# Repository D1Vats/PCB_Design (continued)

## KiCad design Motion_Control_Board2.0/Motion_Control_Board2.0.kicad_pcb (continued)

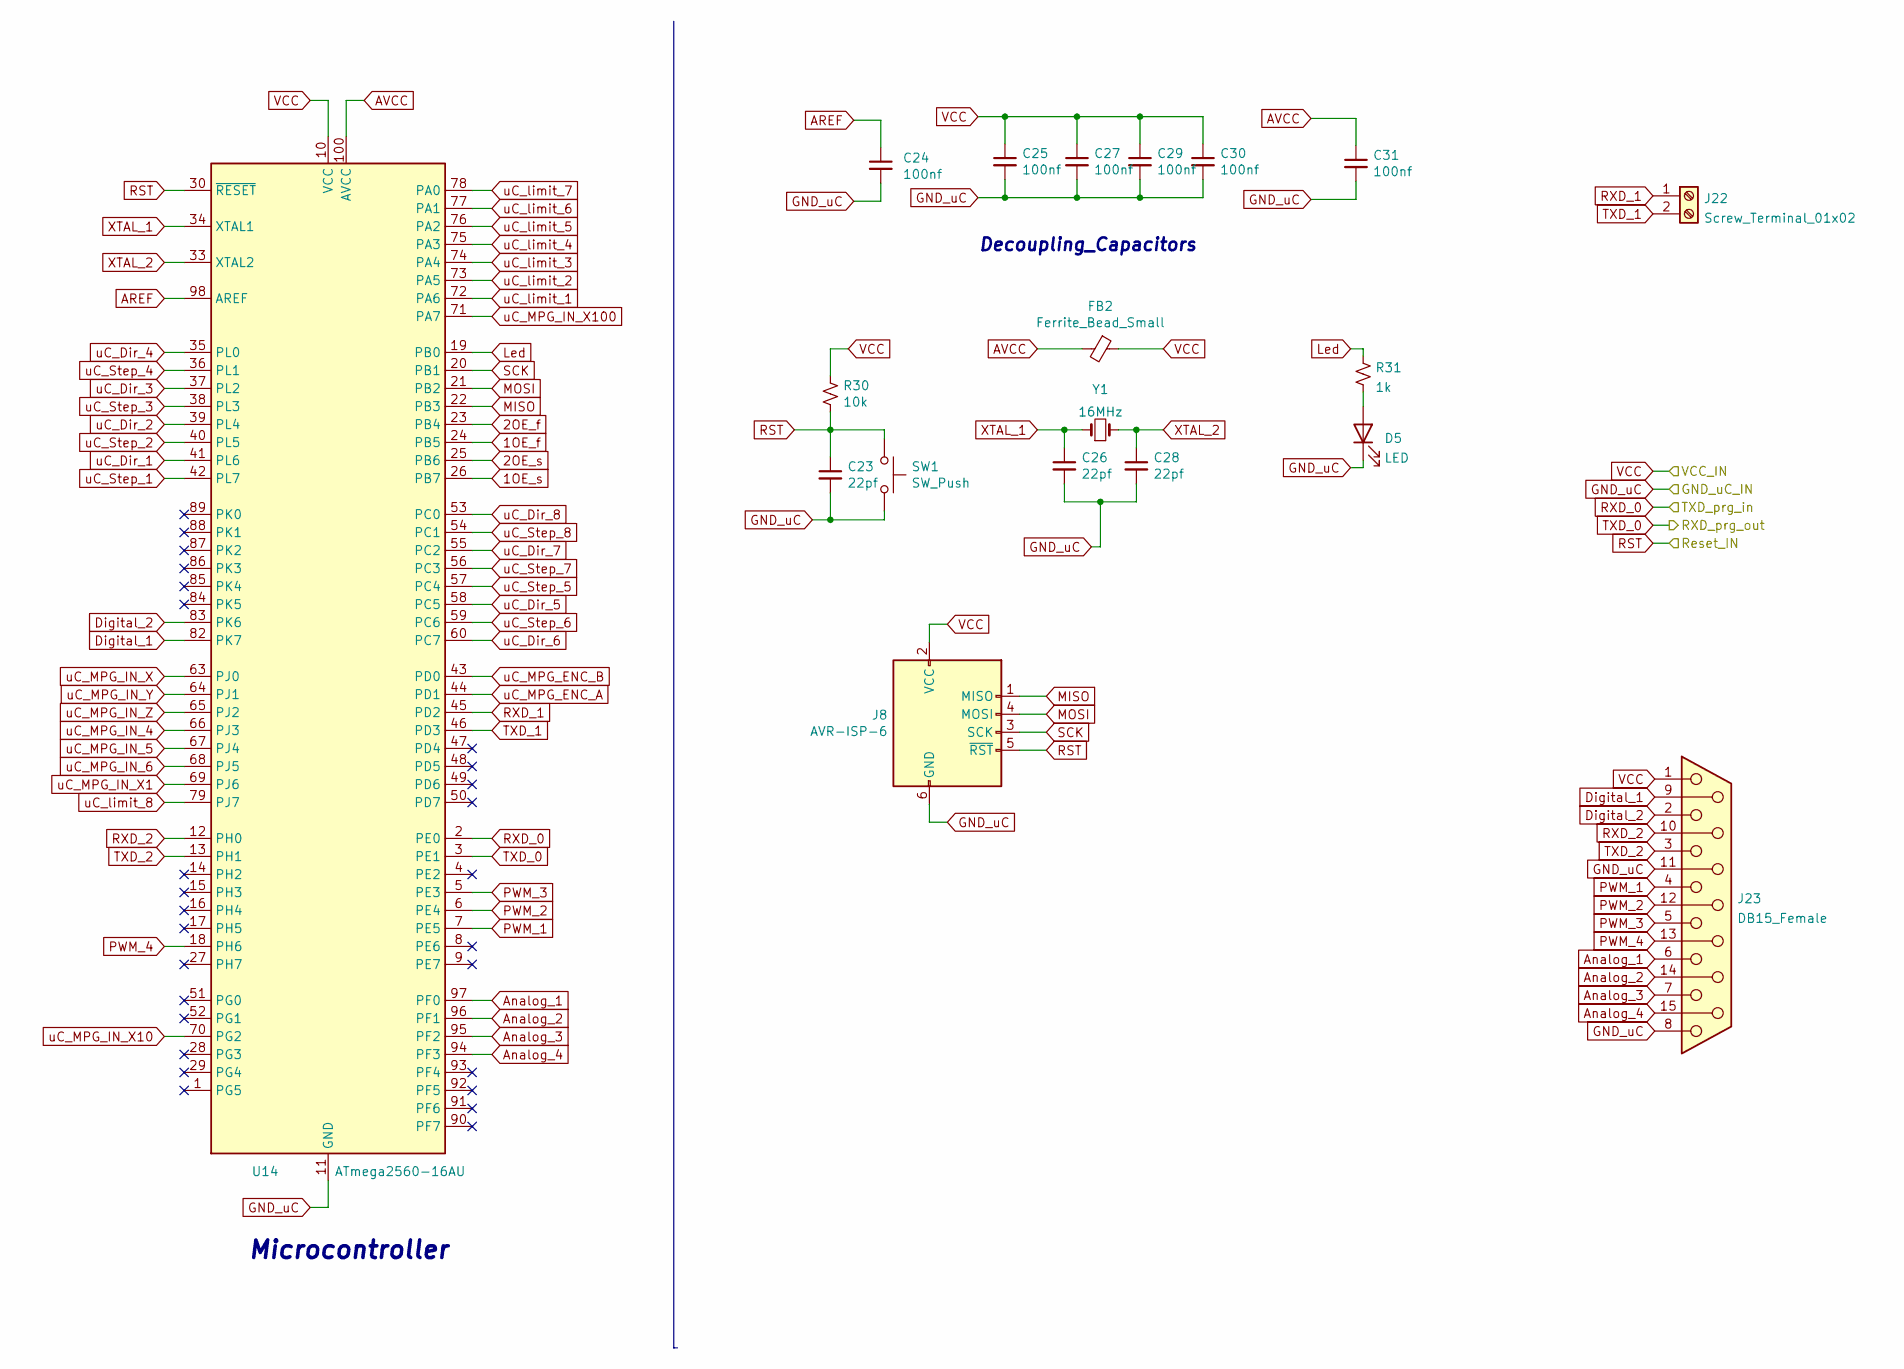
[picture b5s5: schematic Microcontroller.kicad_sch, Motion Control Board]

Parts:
C23, C26, C28: 22pf; C_0805_2012Metric
C24, C25, C27, C29, C30, C31: 100nf; C_0805_2012Metric
D5: LED; LED_0805_2012Metric
FB2: Ferrite_Bead_Small; R_0805_2012Metric
J8: AVR-ISP-6; PinHeader_2x03_P2.54mm_Vertical
J22: Screw_Terminal_01x02; TerminalBlock_4Ucon_1x02_P3.50mm_Vertical
J23: DB15_Female; DSUB-15_Female_Horizontal_P2.77x2.84mm_EdgePinOffset7.70mm_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
R30: 10k; R_0805_2012Metric
R31: 1k; R_0805_2012Metric
SW1: SW_Push; SW_PUSH_6mm
U14: ATmega2560-16AU; TQFP-100_14x14mm_P0.5mm
Y1: 16MHz; Crystal_HC49-4H_Vertical

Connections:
1OE_f: U14.24 (PB5); also elsewhere on the board
1OE_s: U14.26 (PB7); also elsewhere on the board
2OE_f: U14.23 (PB4); also elsewhere on the board
2OE_s: U14.25 (PB6); also elsewhere on the board
5V_OUT_1: C25.1, C27.1, C29.1, C30.1, FB2.1, J8.2 (VCC), J23.1, R30.1, U14.10 (VCC), U14.31 (VCC), U14.61 (VCC), U14.80 (VCC); also elsewhere on the board
AREF: C24.1, U14.98 (AREF)
AVCC: C31.1, FB2.2, U14.100 (AVCC)
Analog_1: J23.6, U14.97 (PF0)
Analog_2: J23.14, U14.96 (PF1)
Analog_3: J23.7, U14.95 (PF2)
Analog_4: J23.15, U14.94 (PF3)
DTR_prg: C23.1, J8.5 (~RST), R30.2, SW1.1, U14.30 (~RESET); also elsewhere on the board
Digital_1: J23.9, U14.82 (PK7)
Digital_2: J23.2, U14.83 (PK6)
Led: R31.1, U14.19 (PB0)
MISO: J8.1 (MISO), U14.22 (PB3)
MOSI: J8.4 (MOSI), U14.21 (PB2)
MPG_GND: C23.2, C24.2, C25.2, C26.2, C27.2, C28.2, C29.2, C30.2, C31.2, D5.1 (K), J8.6 (GND), J23.8, J23.11 (P111), SW1.2, U14.11 (GND), U14.32 (GND), U14.62 (GND), U14.81 (GND), U14.99 (GND); also elsewhere on the board
unnamed: D5.2 (A), R31.2
PWM_1: J23.4, U14.7 (PE5)
PWM_2: J23.12, U14.6 (PE4)
PWM_3: J23.5, U14.5 (PE3)
PWM_4: J23.13, U14.18 (PH6)
RXD_0: U14.2 (PE0); also elsewhere on the board
RXD_1: J22.1, U14.45 (PD2)
RXD_2: J23.10, U14.12 (PH0)
SCK: J8.3 (SCK), U14.20 (PB1)
TXD_0: U14.3 (PE1); also elsewhere on the board
TXD_1: J22.2, U14.46 (PD3)
TXD_2: J23.3, U14.13 (PH1)
XTAL_1: C26.1, U14.34 (XTAL1), Y1.1
XTAL_2: C28.1, U14.33 (XTAL2), Y1.2
uC_Dir_1: U14.41 (PL6); also elsewhere on the board
uC_Dir_2: U14.39 (PL4); also elsewhere on the board
uC_Dir_3: U14.37 (PL2); also elsewhere on the board
uC_Dir_4: U14.35 (PL0); also elsewhere on the board
uC_Dir_5: U14.58 (PC5); also elsewhere on the board
uC_Dir_6: U14.60 (PC7); also elsewhere on the board
uC_Dir_7: U14.55 (PC2); also elsewhere on the board
uC_Dir_8: U14.53 (PC0); also elsewhere on the board
uC_MPG_ENC_A: U14.44 (PD1); also elsewhere on the board
uC_MPG_ENC_B: U14.43 (PD0); also elsewhere on the board
uC_MPG_IN_4: U14.66 (PJ3); also elsewhere on the board
uC_MPG_IN_5: U14.67 (PJ4); also elsewhere on the board
uC_MPG_IN_6: U14.68 (PJ5); also elsewhere on the board
uC_MPG_IN_X: U14.63 (PJ0); also elsewhere on the board
uC_MPG_IN_X1: U14.69 (PJ6); also elsewhere on the board
uC_MPG_IN_X10: U14.70 (PG2); also elsewhere on the board
uC_MPG_IN_X100: U14.71 (PA7); also elsewhere on the board
uC_MPG_IN_Y: U14.64 (PJ1); also elsewhere on the board
uC_MPG_IN_Z: U14.65 (PJ2); also elsewhere on the board
uC_Step_1: U14.42 (PL7); also elsewhere on the board
uC_Step_2: U14.40 (PL5); also elsewhere on the board
uC_Step_3: U14.38 (PL3); also elsewhere on the board
uC_Step_4: U14.36 (PL1); also elsewhere on the board
uC_Step_5: U14.57 (PC4); also elsewhere on the board
uC_Step_6: U14.59 (PC6); also elsewhere on the board
uC_Step_7: U14.56 (PC3); also elsewhere on the board
uC_Step_8: U14.54 (PC1); also elsewhere on the board
uC_limit_1: U14.72 (PA6); also elsewhere on the board
uC_limit_2: U14.73 (PA5); also elsewhere on the board
uC_limit_3: U14.74 (PA4); also elsewhere on the board
uC_limit_4: U14.75 (PA3); also elsewhere on the board
uC_limit_5: U14.76 (PA2); also elsewhere on the board
uC_limit_6: U14.77 (PA1); also elsewhere on the board
uC_limit_7: U14.78 (PA0); also elsewhere on the board
uC_limit_8: U14.79 (PJ7); also elsewhere on the board

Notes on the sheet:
Microcontroller
Decoupling_Capacitors

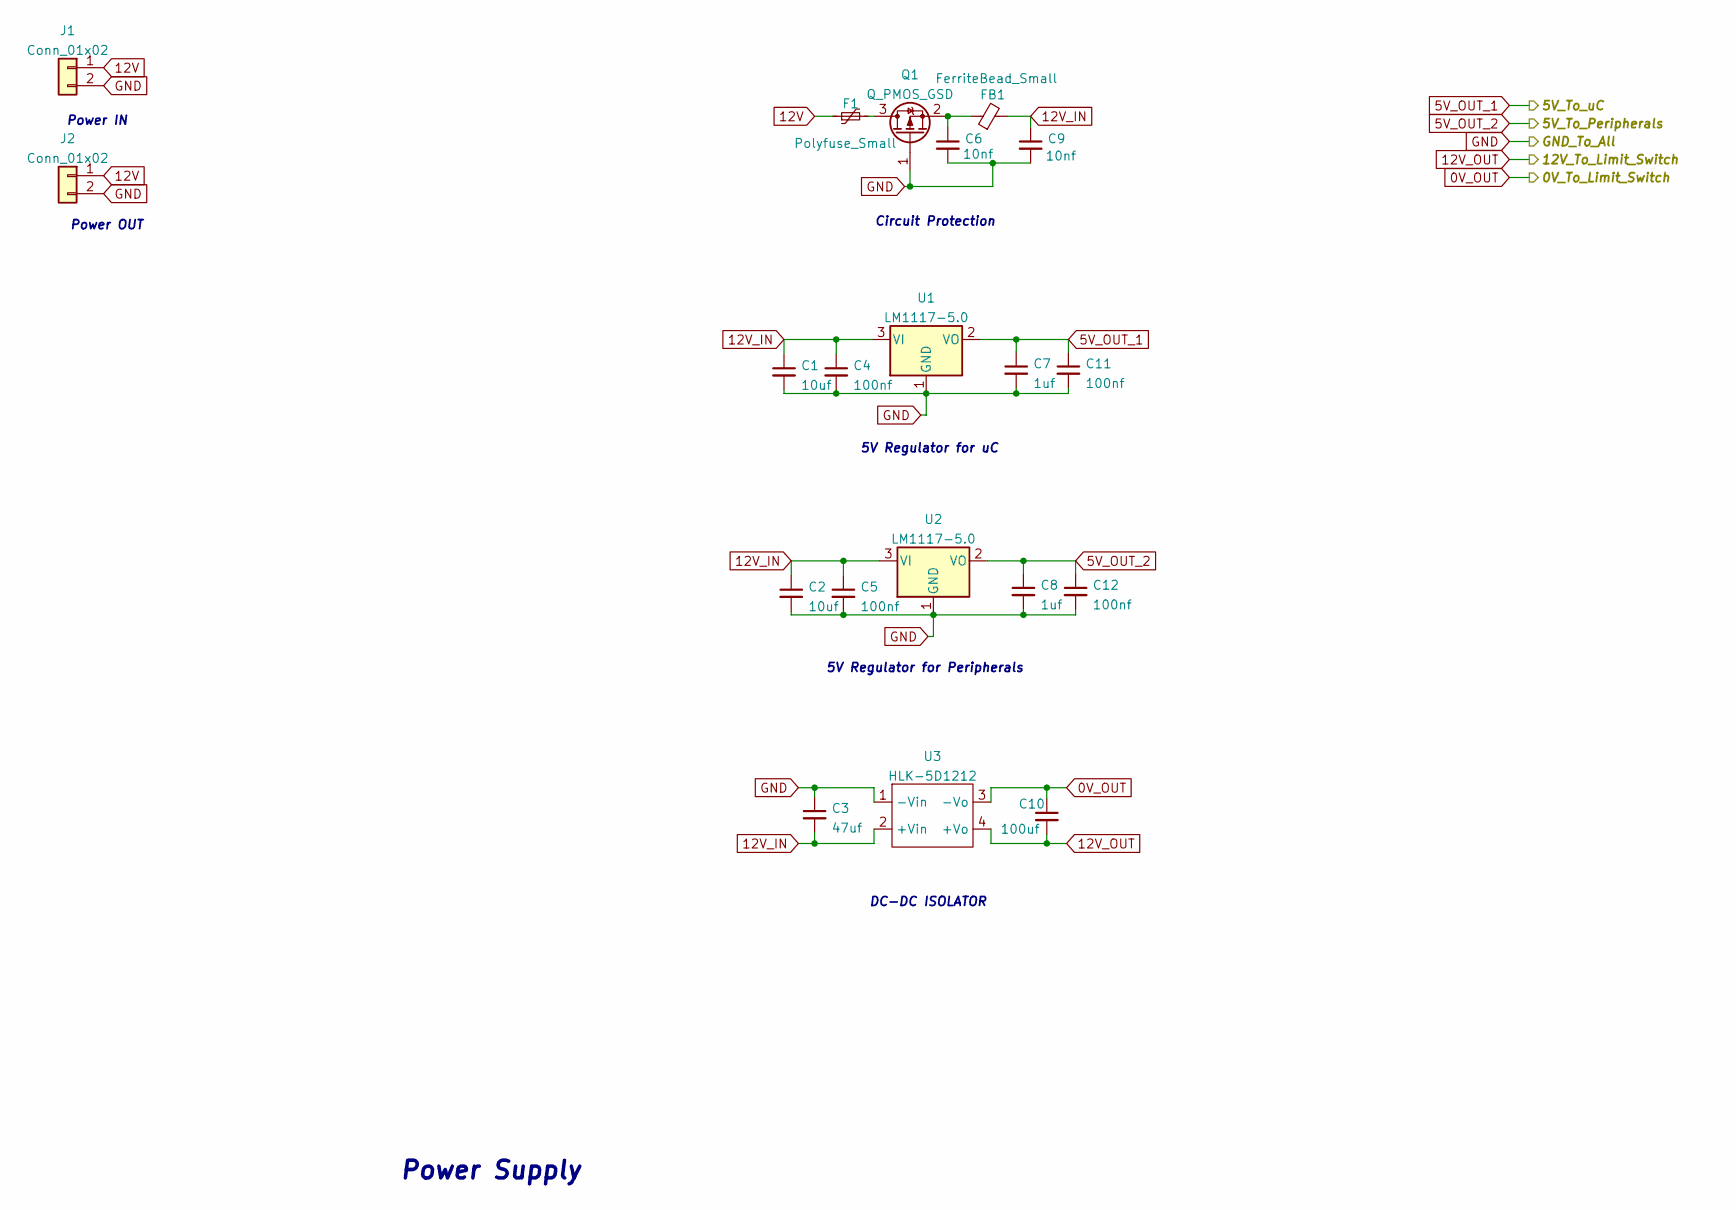
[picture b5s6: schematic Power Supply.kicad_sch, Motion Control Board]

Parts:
C1, C2: 10uf; C_0805_2012Metric
C3: 47uf; C_0805_2012Metric
C4, C5, C11, C12: 100nf; C_0805_2012Metric
C6, C9: 10nf; C_0805_2012Metric
C7, C8: 1uf; C_0805_2012Metric
C10: 100uf; C_0805_2012Metric
F1: Polyfuse_Small; Fuse_0805_2012Metric
FB1: FerriteBead_Small; R_0805_2012Metric
J1, J2: Conn_01x02; TerminalBlock_4Ucon_1x02_P3.50mm_Vertical
Q1: Q_PMOS_GSD; SOT-23W
U1, U2: LM1117-5.0; SOT-223
U3: HLK-5D1212

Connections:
0V_OUT: C10.1, U3.3 (-Vo); also elsewhere on the board
5V_OUT_1: C7.1, C11.1, U1.2 (VO); also elsewhere on the board
5V_OUT_2: C8.1, C12.1, U2.2 (VO); also elsewhere on the board
12V: F1.1, J1.1, J2.1
12V_IN: C1.1, C2.1, C3.2, C4.1, C5.1, C9.1, FB1.2, U1.3 (VI), U2.3 (VI), U3.2 (+Vin)
12V_OUT: C10.2, U3.4 (+Vo); also elsewhere on the board
MPG_GND: C1.2, C2.2, C3.1, C4.2, C5.2, C6.2, C7.2, C8.2, C9.2, C11.2, C12.2, J1.2, J2.2, Q1.1 (G), U1.1 (GND), U2.1 (GND), U3.1 (-Vin); also elsewhere on the board
unnamed: C6.1, FB1.1, Q1.2 (S)
unnamed: F1.2, Q1.3 (D)

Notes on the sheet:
DC-DC ISOLATOR
5V Regulator for uC
5V Regulator for Peripherals
Power OUT
Power Supply
Power IN
Circuit Protection

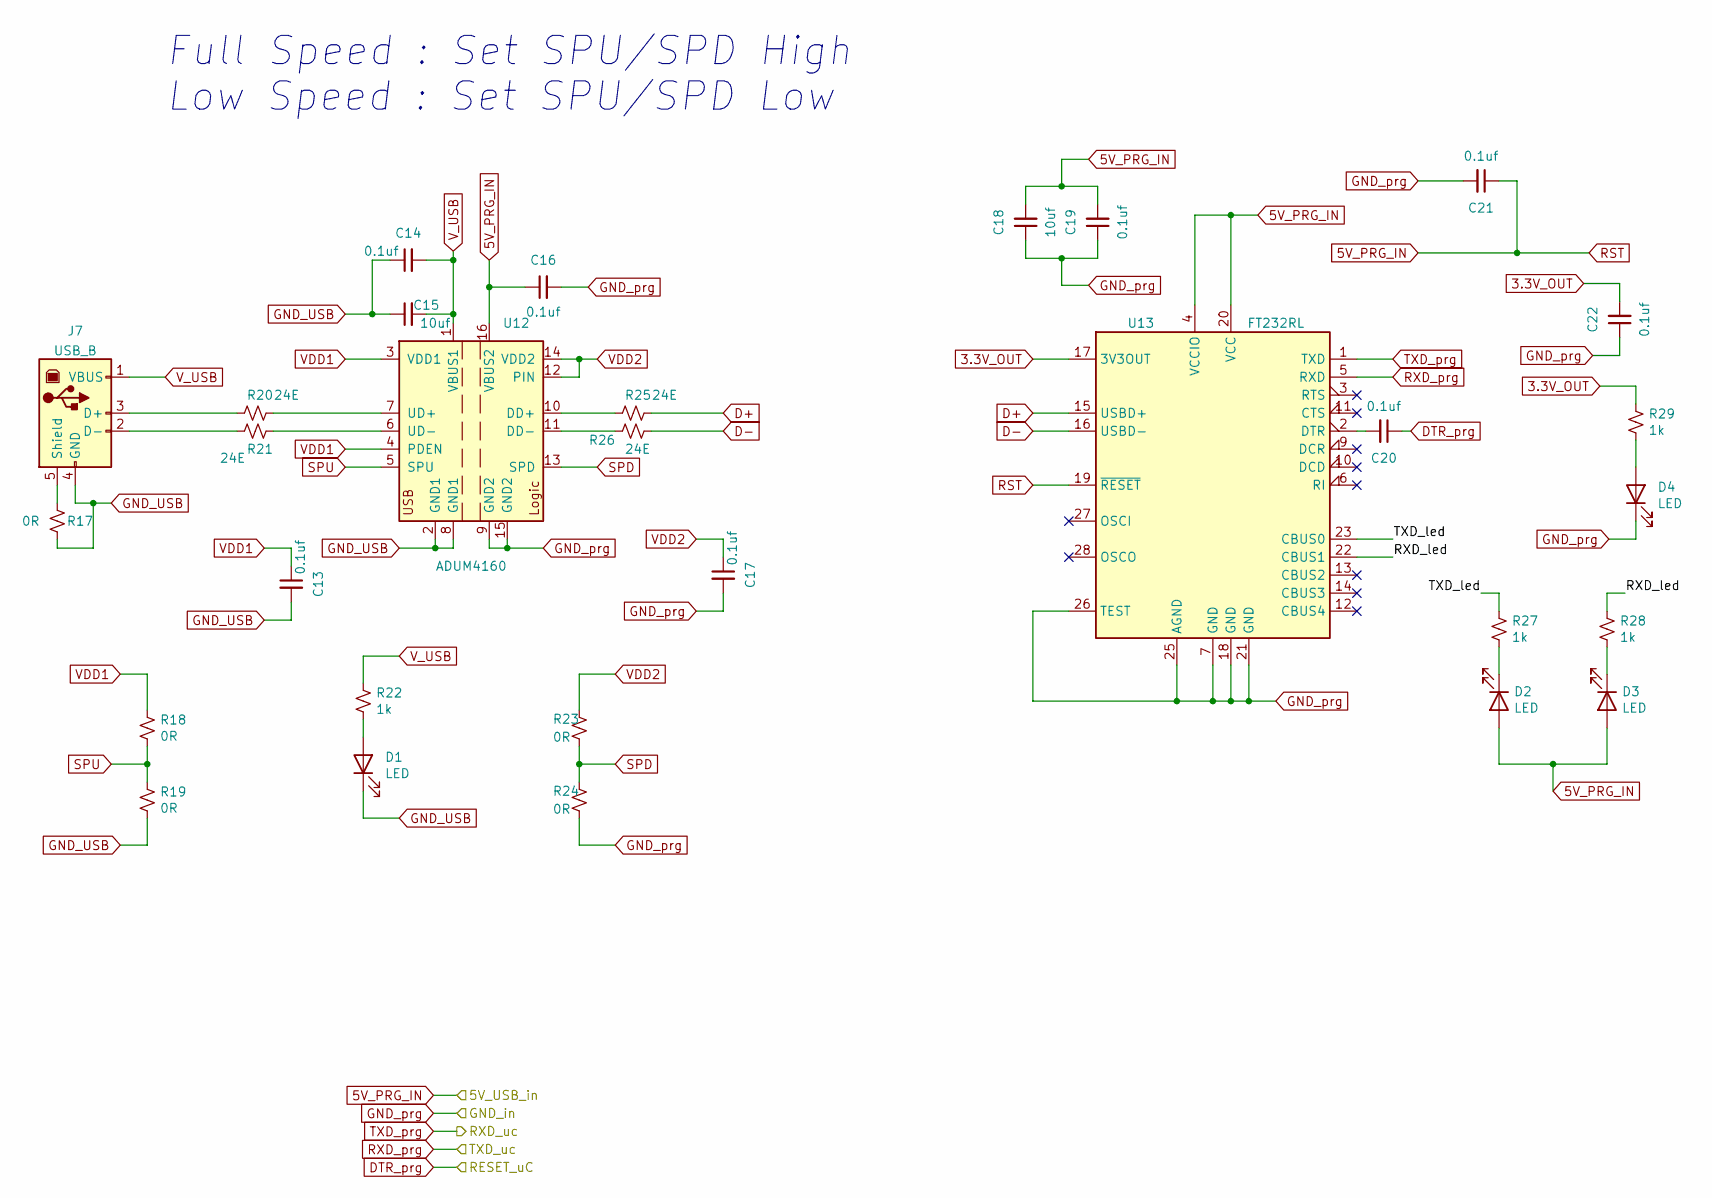
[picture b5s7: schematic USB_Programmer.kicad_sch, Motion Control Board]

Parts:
C13, C14, C16, C17, C19, C20, C21, C22: 0.1uf; C_0805_2012Metric
C15, C18: 10uf; C_0805_2012Metric
D1, D2, D3, D4: LED; LED_0805_2012Metric
J7: USB_B; USB_B_OST_USB-B1HSxx_Horizontal
R17, R18, R19, R23, R24: 0R; R_0805_2012Metric
R20, R21, R25, R26: 24E; R_0805_2012Metric
R22, R27, R28, R29: 1k; R_0805_2012Metric
U12: ADUM4160; SOIC-16W_7.5x10.3mm_P1.27mm
U13: FT232RL; SSOP-28_5.3x10.2mm_P0.65mm

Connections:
3.3V_OUT: C22.2, R29.1, U13.17 (3V3OUT)
5V_OUT_1: C16.1, C18.2, C19.2, C21.1, D2.2 (A), D3.2 (A), U12.16 (VBUS2), U13.4 (VCCIO), U13.19 (~RESET), U13.20 (VCC); also elsewhere on the board
/USB_Programmer/RXD_led: R28.1, U13.22 (CBUS1)
/USB_Programmer/TXD_led: R27.1, U13.23 (CBUS0)
D+: R25.1, U13.15 (USBD+)
D-: R26.1, U13.16 (USBD-)
DTR_prg: C20.1; also elsewhere on the board
GND_USB: C13.2, C14.1, C15.1, D1.1 (K), J7.4 (GND), R17.2, R19.2, U12.2 (GND1), U12.8 (GND1)
MPG_GND: C16.2, C17.2, C18.1, C19.1, C21.2, C22.1, D4.1 (K), R24.2, U12.9 (GND2), U12.15 (GND2), U13.7 (GND), U13.18 (GND), U13.21 (GND), U13.25 (AGND), U13.26 (TEST); also elsewhere on the board
unnamed: C20.2, U13.2 (DTR)
unnamed: D1.2 (A), R22.2
unnamed: D2.1 (K), R27.2
unnamed: D3.1 (K), R28.2
unnamed: D4.2 (A), R29.2
unnamed: J7.2 (D-), R21.2
unnamed: J7.3 (D+), R20.2
unnamed: J7.5 (Shield), R17.1
unnamed: R20.1, U12.7 (UD+)
unnamed: R21.1, U12.6 (UD-)
unnamed: R25.2, U12.10 (DD+)
unnamed: R26.2, U12.11 (DD-)
RXD_0: U13.1 (TXD); also elsewhere on the board
SPD: R23.2, R24.1, U12.13 (SPD)
SPU: R18.2, R19.1, U12.5 (SPU)
TXD_0: U13.5 (RXD); also elsewhere on the board
VDD1: C13.1, R18.1, U12.3 (VDD1), U12.4 (PDEN)
VDD2: C17.1, R23.1, U12.12 (PIN), U12.14 (VDD2)
V_USB: C14.2, C15.2, J7.1 (VBUS), R22.1, U12.1 (VBUS1)

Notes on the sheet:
Full Speed : Set SPU/SPD High Low Speed : Set SPU/SPD Low

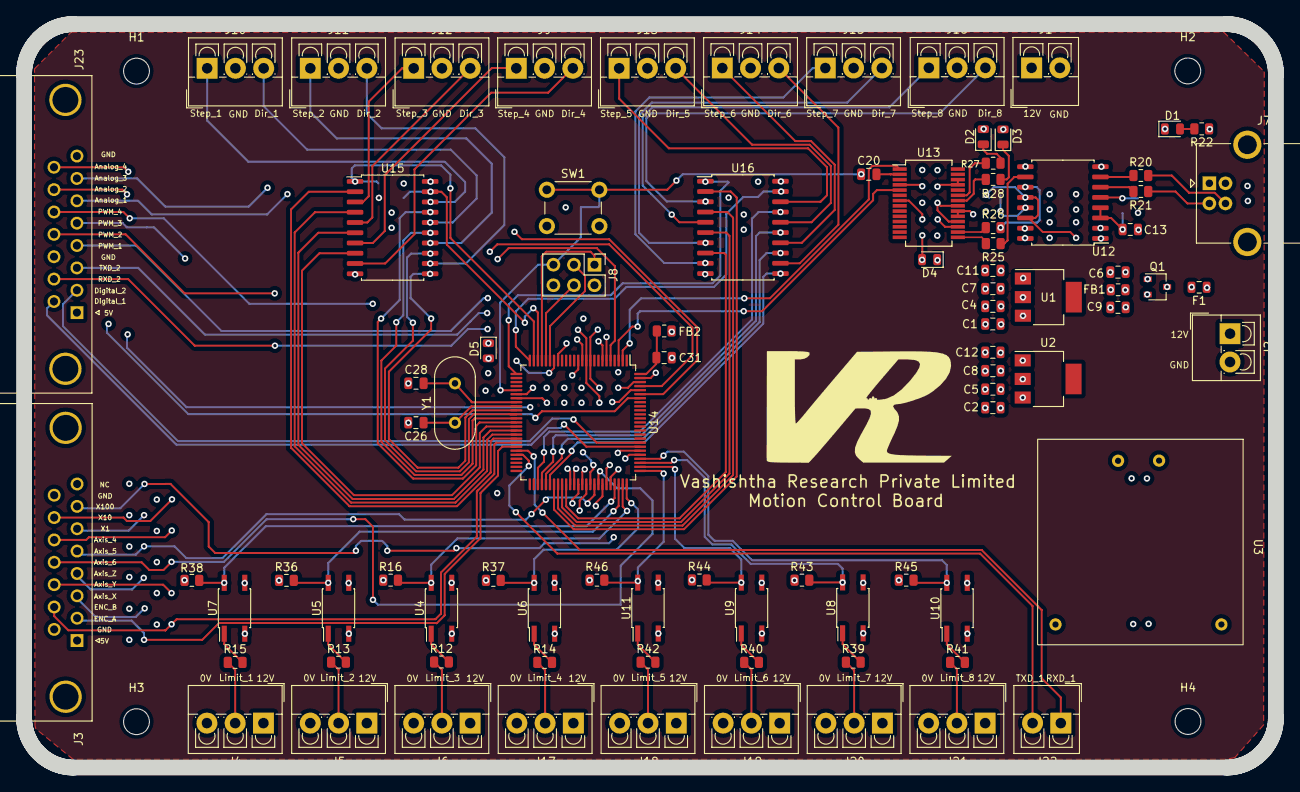
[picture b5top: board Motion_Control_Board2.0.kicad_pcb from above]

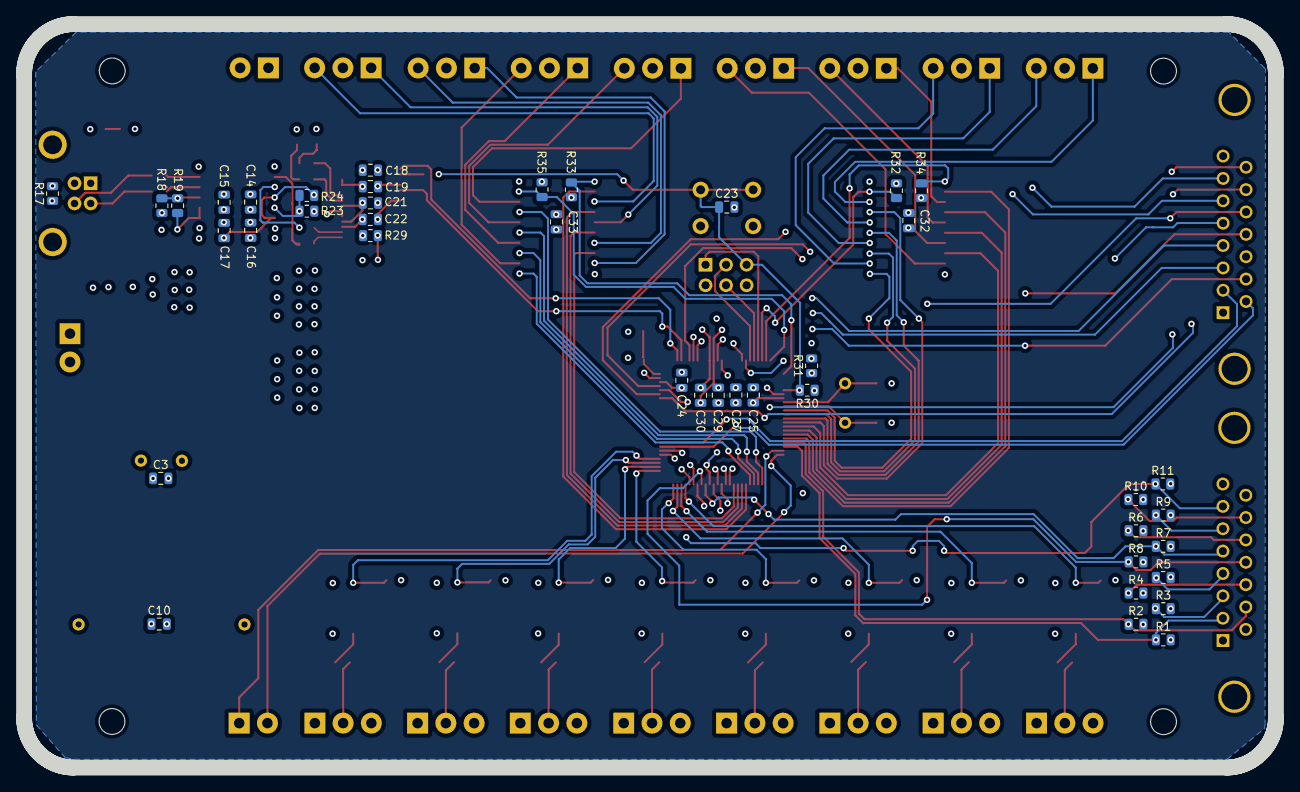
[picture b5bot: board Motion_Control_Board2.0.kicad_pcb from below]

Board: 4 copper layers, 155.0 x 92.1 mm, 133 parts (41 on the bottom side), 129 nets.

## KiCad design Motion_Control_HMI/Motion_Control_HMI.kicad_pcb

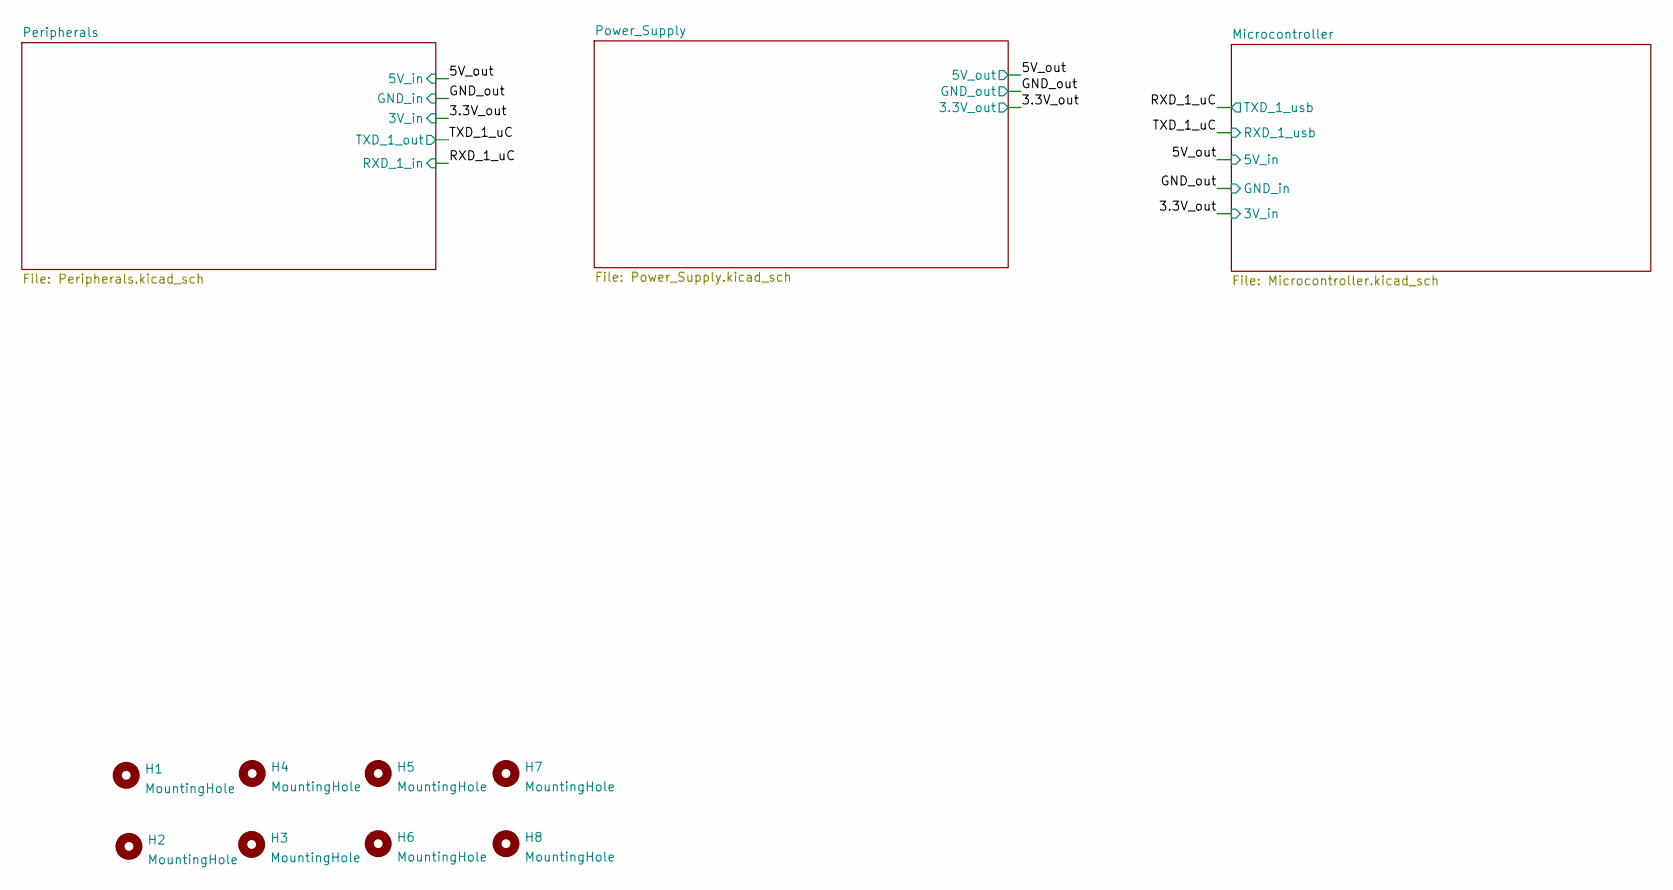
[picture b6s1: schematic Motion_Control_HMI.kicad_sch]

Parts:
H1, H3, H4, H6: MountingHole; MountingHole_4.3mm_M4
H2, H5, H7, H8: MountingHole; MountingHole_3.2mm_M3

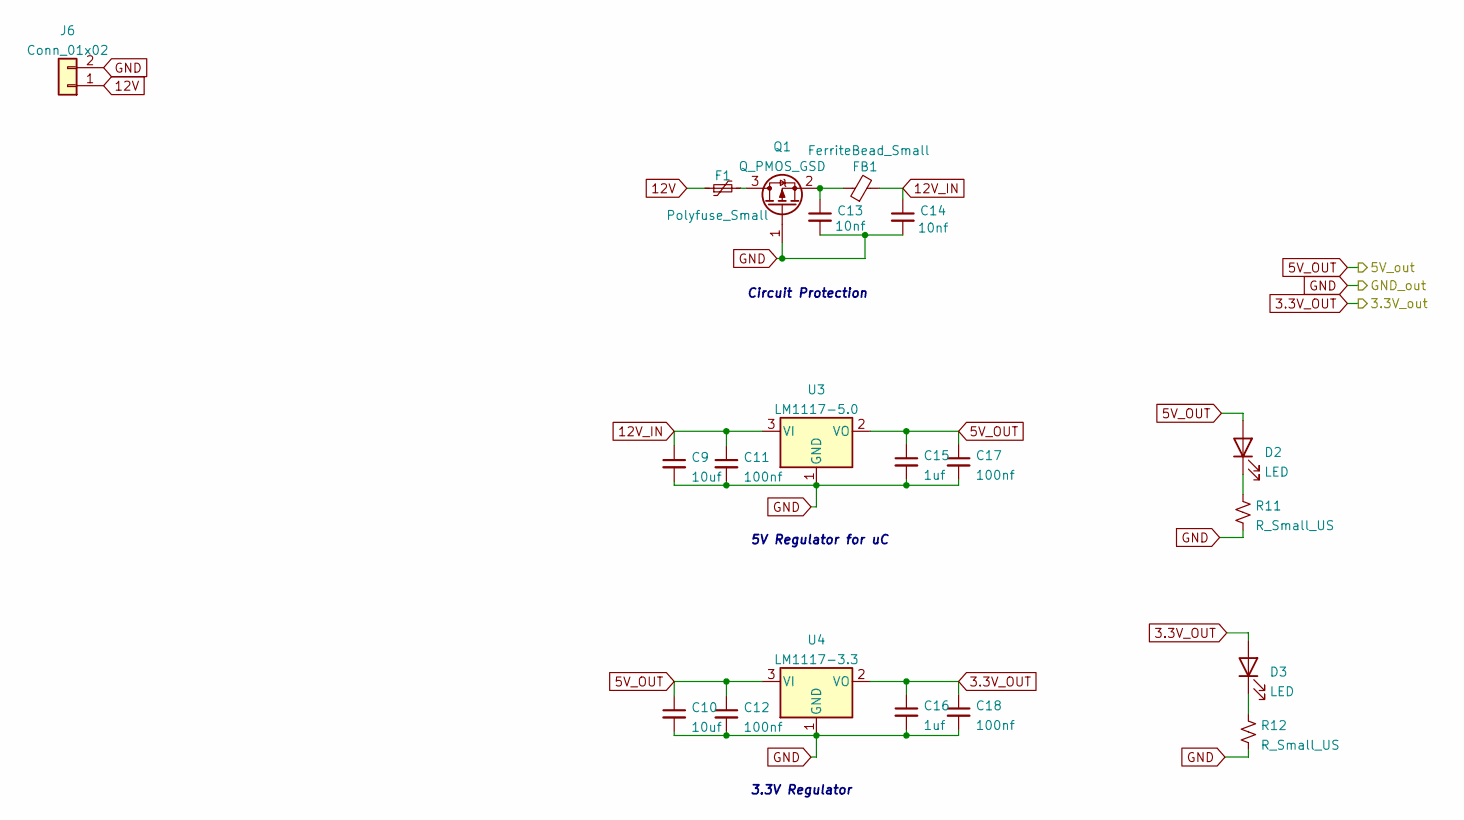
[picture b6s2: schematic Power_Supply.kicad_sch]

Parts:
C9, C10: 10uf; C_0805_2012Metric
C11, C12, C17, C18: 100nf; C_0805_2012Metric
C13, C14: 10nf; C_0805_2012Metric
C15, C16: 1uf; C_0805_2012Metric
D2, D3: LED; LED_0805_2012Metric
F1: Polyfuse_Small; Fuse_0805_2012Metric
FB1: FerriteBead_Small; R_0805_2012Metric
J6: Conn_01x02; JST_EH_B2B-EH-A_1x02_P2.50mm_Vertical
Q1: Q_PMOS_GSD; SOT-23W
R11, R12: R_Small_US; R_0805_2012Metric
U3: LM1117-5.0; SOT-223
U4: LM1117-3.3; SOT-223

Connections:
3.3V_OUT: C16.1, C18.1, D3.2 (A), U4.2 (VO); also elsewhere on the board
5v: C10.1, C12.1, C15.1, C17.1, D2.2 (A), U3.2 (VO), U4.3 (VI); also elsewhere on the board
12V: F1.1, J6.1
12V_IN: C9.1, C11.1, C14.1, FB1.2, U3.3 (VI)
GND: C9.2, C10.2, C11.2, C12.2, C13.2, C14.2, C15.2, C16.2, C17.2, C18.2, J6.2, Q1.1 (G), R11.2, R12.2, U3.1 (GND), U4.1 (GND); also elsewhere on the board
unnamed: C13.1, FB1.1, Q1.2 (S)
unnamed: D2.1 (K), R11.1
unnamed: D3.1 (K), R12.1
unnamed: F1.2, Q1.3 (D)

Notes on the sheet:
5V Regulator for uC
Circuit Protection
3.3V Regulator

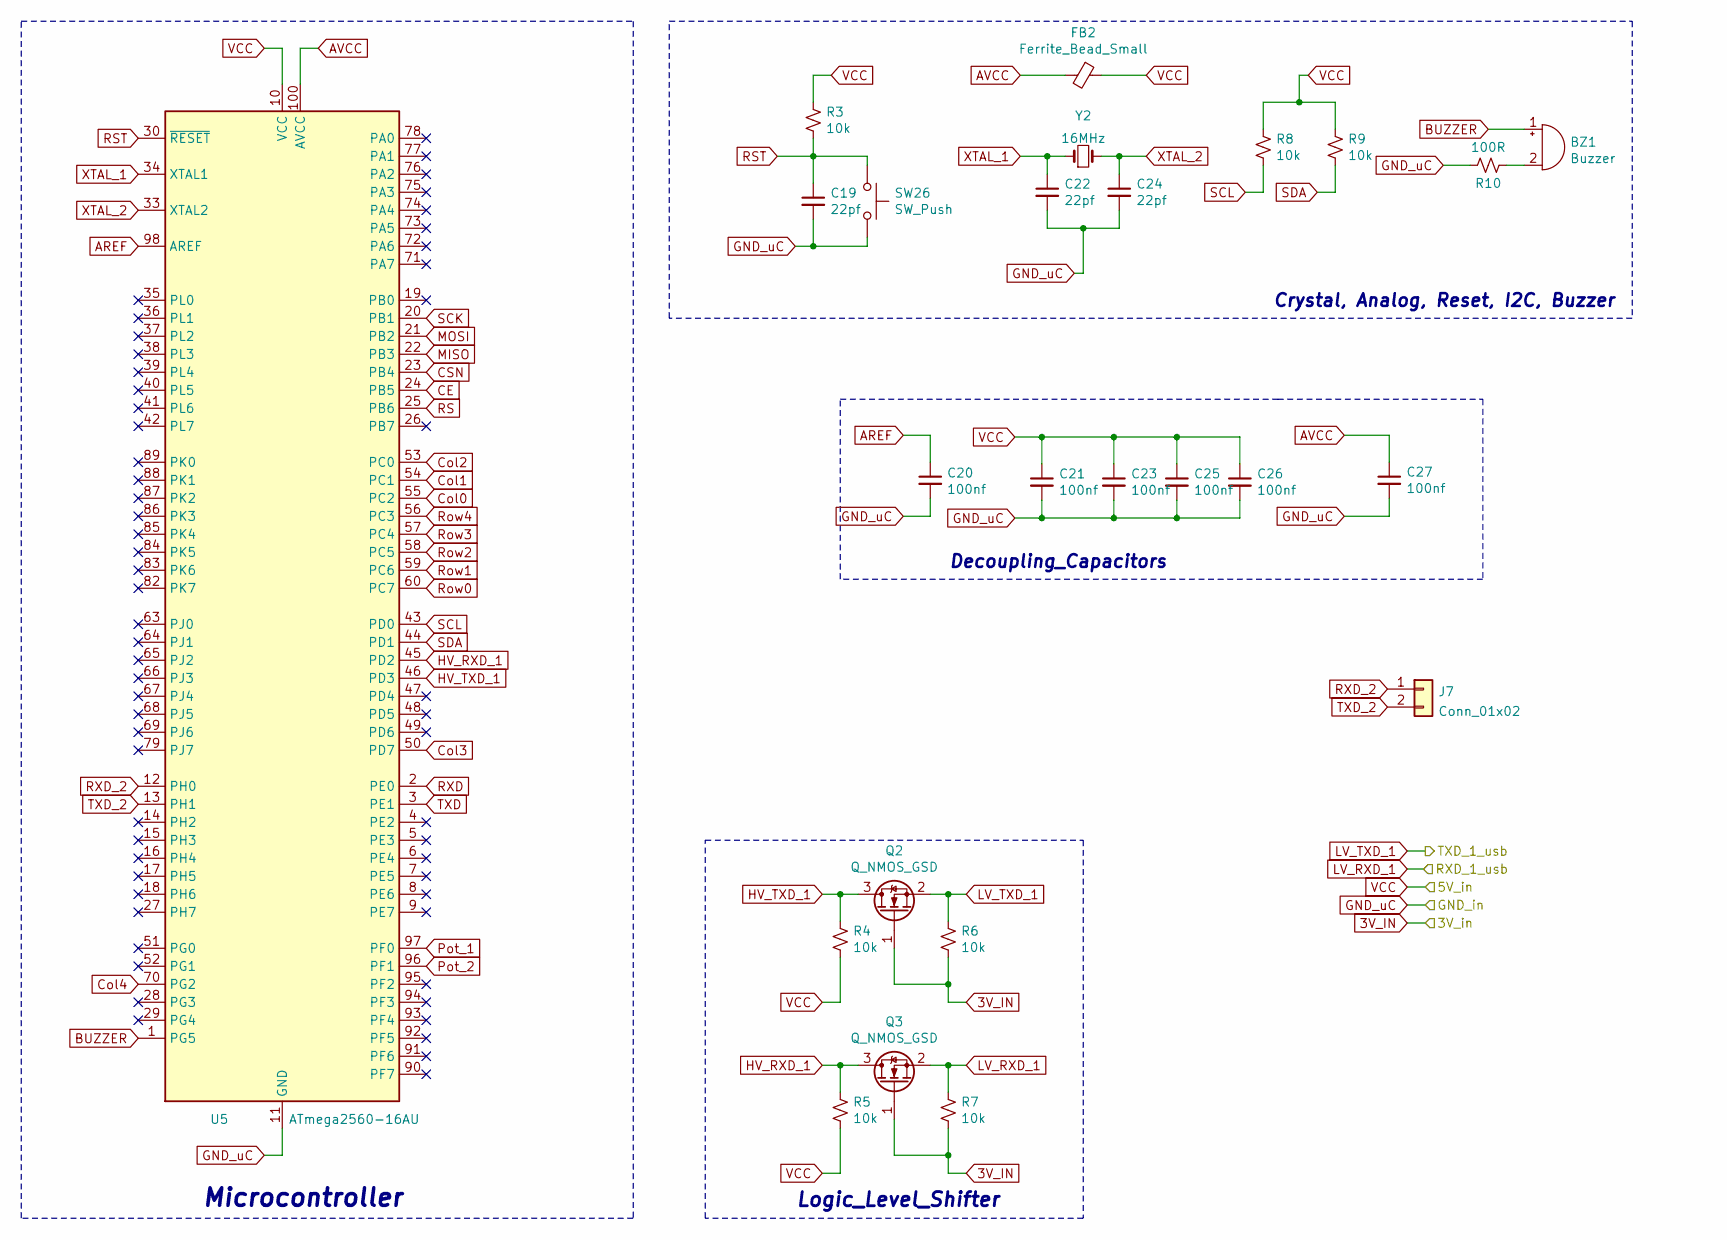
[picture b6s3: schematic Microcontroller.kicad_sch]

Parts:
BZ1: Buzzer; Buzzer_12x9.5RM7.6
C19, C22, C24: 22pf; C_0805_2012Metric
C20, C21, C23, C25, C26, C27: 100nf; C_0805_2012Metric
FB2: Ferrite_Bead_Small; R_0805_2012Metric
J7: Conn_01x02; JST_EH_B2B-EH-A_1x02_P2.50mm_Vertical
Q2, Q3: Q_NMOS_GSD; SOT-23W
R3, R4, R5, R6, R7, R8, R9: 10k; R_0805_2012Metric
R10: 100R; R_0805_2012Metric
SW26: SW_Push; Key_Dome
U5: ATmega2560-16AU; TQFP-100_14x14mm_P0.5mm
Y2: 16MHz; Crystal_HC49-4H_Vertical

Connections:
3.3V_OUT: Q2.1 (G), Q3.1 (G), R6.2, R7.2; also elsewhere on the board
5v: C21.1, C23.1, C25.1, C26.1, FB2.1, R3.1, R4.2, R5.2, R8.1, R9.1, U5.10 (VCC), U5.31 (VCC), U5.61 (VCC), U5.80 (VCC); also elsewhere on the board
AREF: C20.1, U5.98 (AREF)
AVCC: C27.1, FB2.2, U5.100 (AVCC)
BUZZER: BZ1.1 (-), U5.1 (PG5)
CE: U5.24 (PB5); also elsewhere on the board
CSN: U5.23 (PB4); also elsewhere on the board
Col0: U5.55 (PC2); also elsewhere on the board
Col1: U5.54 (PC1); also elsewhere on the board
Col2: U5.53 (PC0); also elsewhere on the board
Col3: U5.50 (PD7); also elsewhere on the board
Col4: U5.70 (PG2); also elsewhere on the board
GND: C19.2, C20.2, C21.2, C22.2, C23.2, C24.2, C25.2, C26.2, C27.2, R10.2, SW26.2, U5.11 (GND), U5.32 (GND), U5.62 (GND), U5.81 (GND), U5.99 (GND); also elsewhere on the board
HV_RXD_1: Q3.3 (D), R5.1, U5.45 (PD2)
HV_TXD_1: Q2.3 (D), R4.1, U5.46 (PD3)
LV_TXD_1: Q2.2 (S), R6.1; also elsewhere on the board
MISO: U5.22 (PB3); also elsewhere on the board
MOSI: U5.21 (PB2); also elsewhere on the board
unnamed: BZ1.2 (+), R10.1
Pot_1: U5.97 (PF0); also elsewhere on the board
Pot_2: U5.96 (PF1); also elsewhere on the board
RS: U5.25 (PB6); also elsewhere on the board
RST: C19.1, R3.2, SW26.1, U5.30 (~RESET); also elsewhere on the board
RXD: U5.2 (PE0); also elsewhere on the board
RXD_2: J7.1, U5.12 (PH0)
Row0: U5.60 (PC7); also elsewhere on the board
Row1: U5.59 (PC6); also elsewhere on the board
Row2: U5.58 (PC5); also elsewhere on the board
Row3: U5.57 (PC4); also elsewhere on the board
Row4: U5.56 (PC3); also elsewhere on the board
SCK: U5.20 (PB1); also elsewhere on the board
SCL: R8.2, U5.43 (PD0); also elsewhere on the board
SDA: R9.2, U5.44 (PD1); also elsewhere on the board
TXD: U5.3 (PE1); also elsewhere on the board
TXD_1: Q3.2 (S), R7.1; also elsewhere on the board
TXD_2: J7.2, U5.13 (PH1)
XTAL_1: C22.1, U5.34 (XTAL1), Y2.1
XTAL_2: C24.1, U5.33 (XTAL2), Y2.2

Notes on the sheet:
Microcontroller
Logic_Level_Shifter
Decoupling_Capacitors
Crystal, Analog, Reset, I2C, Buzzer
